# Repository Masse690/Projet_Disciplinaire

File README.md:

# Projet Smart Campus

Projet de terminal connecté intelligent développé dans le cadre du **Projet Disciplinaire M2** à l'Université Côte d'Azur.

Ce dépôt rassemble les documents de conception d'un nœud IoT alimenté par récupération d'énergie solaire. Le démonstrateur associera un module LoRaWAN RAK3172, un gestionnaire d'énergie bq25570, un stockage d'énergie et un ou plusieurs capteurs pour surveiller un environnement du campus.

> **Statut actuel :** sujet, architecture de base et datasheets disponibles. Le firmware, la conception KiCad, le PCB, l'antenne, le boîtier 3D et les résultats de démonstration restent à ajouter.

---

## Vue d'ensemble

L'objectif du projet est de concevoir un objet connecté autonome, depuis le choix des composants jusqu'à sa validation sur le réseau LoRaWAN.

Le projet couvre les étapes suivantes :

- conception du hardware avec KiCad ;
- intégration de capteurs ;
- développement du firmware embarqué ;
- conception et optimisation de l'antenne ;
- création d'un boîtier imprimé en 3D ;
- alimentation par panneau solaire ;
- stockage de l'énergie dans un supercondensateur ou une batterie ;
- fabrication du PCB ;
- assemblage des composants ;
- déploiement d'une démonstration sur une durée de une à deux semaines ;
- validation des communications et de la consommation énergétique.

### Architecture cible

```text
Panneau solaire
      |
      v
   bq25570
   +------+
   |      +--> stockage d'énergie
   |      |    (supercondensateur ou batterie)
   |      |
   |      +--> alimentation 3,3 V
   +------+
      |
      v
+-------------------+
| RAK3172 / STM32WL|<--> antenne LoRa 868 MHz
+-------------------+
      |
      +--> capteur(s) I2C/UART
```

---

## Équipe

| Nom | Rôle |
|---|---|
| Noé Massé | Firmware, électronique, capteurs, réseau |
| Alec Passolunghi | Conception PCB, boîtier 3D |
| Matis Chevreaux | Antenne |

**Encadrement :** 
- Fabien Ferrero — Université Côte d'Azur / CNRS / LEAT
- Dorian Diana — Université Côte d'Azur / LEAT
---

## Cas d'application

Le sujet propose l'utilisation d'au moins un capteur spécifique au projet. Les ressources initiales du dépôt comprennent une datasheet pour le capteur de gaz MQ-2.

Usages possibles :

- détection de fumée dans une salle ;
- surveillance de la qualité de l'air ;
- détection de fuite de gaz ;
- alerte de sécurité dans un bâtiment ;

L'application retenue, .... à definir

---

## Architecture matérielle

### Contrôleur et radio

Le **RAK3172** est un module LoRaWAN compact basé sur le microcontrôleur STM32WLE5CC.

Caractéristiques principales :

- cœur ARM Cortex-M4 jusqu'à 48 MHz ;
- radio LoRa / LoRaWAN ;
- support LoRaWAN 1.0.3 ;
- modes OTAA et ABP ;
- communication P2P ;
- interfaces UART, I2C et GPIO ;
- tension d'alimentation comprise entre 2,0 V et 3,6 V ;
- connexion à une antenne 868 MHz par réseau RF dédié.

Exemples de consommations indiquées dans la datasheet :

| Mode | Valeur indicative |
|---|---:|
| Sleep | 1,69 µA |
| Réception | 5,22 mA |
| Émission | environ 87 mA à 20 dBm |

La valeur finale devra être mesurée sur le prototype assemblé.

### Gestion d'énergie

Le **bq25570** est un chargeur ultra-faible consommation pour applications alimentées par récupération d'énergie.

Fonctions principales :

- démarrage à froid à partir d'environ 600 mV ;
- fonctionnement normal à partir d'environ 100 mV ;
- suivi du point de puissance maximale programmable ;
- protection de la tension de batterie ;
- sortie buck régulée ;
- surcharge, sous-charge et gestion du stockage.

L'étage bq25570 doit permettre d'alimenter la charge électronique pendant les périodes de faible ensoleillement grâce à un stockage tampon.

### Stockage d'énergie

Deux solutions peuvent être utilisées :

- supercondensateur ;
- batterie rechargeable.

La datasheet du bq25570 indique qu'une capacité équivalente d'au moins 100 µF est nécessaire. Le stockage, sa tension maximale, sa capacité utile et ses limites de charge devront être choisis selon le profil d'utilisation.

### Capteur MQ-2

Le MQ-2 est un capteur semi-conducteur sensible aux gaz combustibles et à la fumée.

Gaz détectables :

- GPL ;
- propane ;
- butane ;
- méthane ;
- hydrogène ;
- alcool ;
- fumée ;
- monoxyde de carbone.

Considérations d'intégration :

- alimentation/heater : environ 5 V ;
- consommation du heater : inférieure à 800 mW ;
- résistance de détection typique : 3 à 30 kΩ ;
- préchauffage recommandé : au moins 24 heures ;
- calibration nécessaire avec des concentrations de gaz connues ;
- densité de gaz à confirmer dans l'utilisation finale.

Le MQ-2 est principalement adapté à une détection relative. Les valeurs brutes doivent être calibrées plutôt que directement interprétées comme une concentration précise.

---

## Développement logiciel

La plateforme peut être programmée depuis l'environnement Arduino ou depuis les outils ST, selon le firmware retenu.

Fonctions prévues :

- initialisation du RAK3172 ;
- activation LoRaWAN ;
- acquisition périodique des capteurs ;
- conversion et calibration des mesures ;
- gestion des valeurs limites ;
- transmission via OTAA ou ABP ;
- gestion des accusés de réception ;
- configuration des périodes de sommeil ;
- adaptation du taux de transmission ;
- surveillance de la tension de stockage ;
- journalisation des événements.

Des exemples de scripts, d'envoi de données et de visualisation pourront être ajoutés dans ce dépôt lorsque l'application sera implémentée.

---

## Communications LoRaWAN

Le nœud pourra joindre un réseau LoRaWAN en utilisant OTAA ou ABP.

Les informations suivantes devront être définies pour chaque déploiement :

- région LoRaWAN ;
- identifiants OTAA ou clés ABP ;
- classe de terminal ;
- fréquence d'émission ;
- facteur d'étalement ;
- bande passante ;
- cycle de mesure ;
- payload ;
- serveur réseau ;
- application Node-RED ou serveur de visualisation.

Les clés réseau ne doivent jamais être publiées dans ce dépôt. Elles devront être stockées dans un fichier ignoré par Git ou injectées localement lors de la compilation.

---

## Antenne et conception du boîtier

### Antenne

La carte devra intégrer une solution adaptée à la fréquence choisie, généralement 868 MHz en Europe.

Travaux à réaliser :

- étude de l'impédance ;
- choix du type d'antenne ;
- optimisation dans son environnement réel ;
- mesure du diagramme ou de l'adaptation si un équipement est disponible ;
- distance entre l'antenne, le plan de masse, le panneau solaire et les composants sensibles.

### Boîtier

Le boîtier imprimé en 3D devra :

- protéger l'électronique ;
- permettre le passage ou l'intégration de l'antenne ;
- protéger le capteur tout en laissant l'air circuler ;
- faciliter l'orientation du panneau solaire ;
- permettre l'accès aux connecteurs de programmation ;
- intégrer des éventuelles fixations pour le Smart Campus.

---

## Conception PCB

La carte finale sera conçue avec KiCad et réalisée pour l'assemblage du démonstrateur.

Livrables attendus :

- schéma électrique ;
- annotation des composants ;
- liste BOM ;
- routage du PCB ;
- fichiers Gerber ;
- fichier de perçage ;
- fichiers Pick-and-Place ;
- plan de masse ;
- respect de l'intégrité RF ;
- plan d'essai et de programmation ;
- documentation d'assemblage.

Ces fichiers seront ajoutés au dépôt une fois la première révision validée.

---

## Structure du dépôt

```text
.
├── Data_sheet/                 # Datasheets des composants
│   ├── 605-00008-MQ-2-Datasheet-370464.pdf
│   ├── bq25570.pdf
│   └── RAK3172.pdf
├── Projet SMART CAMPUS_27.pdf  # Sujet du projet
└── README.md
```

Structure cible :

```text
.
├── hardware/
│   ├── schematics/
│   ├── kicad/
│   ├── gerber/
│   ├── bom/
│   └── 3d/
├── datasheets/
├── firmware/
├── application/
├── tests/
├── photos/
└── README.md
```

---

## Tests et validation

Les validations prévues comprennent :

- vérification du schéma et du routage ;
- test de démarrage du bq25570 ;
- mesure des tensions de stockage ;
- test du buck 3,3 V ;
- test de préchauffage du MQ-2 ;
- calibration du capteur ;
- vérification du courant sommeil ;
- mesure du courant de réception ;
- mesure du courant d'émission ;
- test OTAA ou ABP ;
- validation de la portée ;
- démonstration extérieure ;
- analyse de l'autonomie sur plusieurs jours ;
- mesures de consommation avec les temporisations réelles.

Les résultats seront accompagnés de captures, tableaux ou graphiques dès qu'ils seront disponibles.

---

## Installation

### Prérequis prévus

- Arduino IDE avec le cœur RAKwireless, ou environnement STM32 compatible ;
- KiCad pour consulter ou modifier les fichiers hardware ;
- outil de terminal série ;
- compte réseau LoRaWAN ;
- chaîne d'alimentation solaire adaptée ;
- chargeur ou alimentation pour les essais.

### Firmware

Le firmware n'est pas encore ajouté au dépôt. Une fois disponible, cette section devra fournir :

```text
git clone https://github.com/Masse690/Projet_Disciplinaire.git
cd Projet_Disciplinaire
```

Puis les instructions exactes d'installation des dépendances, de compilation et de téléversement.

---

## Critères d'évaluation

| Critère | Pondération |
|---|---:|
| Technique : complexité du système | 30 % |
| Applicabilité : maturité et utilité du démonstrateur | 25 % |
| Présentation : qualité, clarté et réponses aux questions | 25 % |
| Consommation : optimisation énergétique | 20 % |

---

## Planning

| Période | Travaux |
|---|---|
| Phase actuelle | Analyse du sujet, composants et architecture |
| À venir | Sélection finale du cas d'application et du capteur |
| À venir | Modélisation et conception de l'antenne |
| À venir | Développement du firmware |
| À venir | Conception PCB sous KiCad |
| Décembre 2026 | Finalisation de la carte électronique |
| Janvier 2027 | Fabrication de la carte |
| À venir | Assemblage avec pochoir et four à fusion |
| À venir | Tests électriques, LoRaWAN et autonomie |
| À venir | Déploiement sur une à deux semaines |

---

## Ressources

- [Sujet du projet](Projet%20SMART%20CAMPUS_27.pdf)
- [Datasheet RAK3172](Data_sheet/RAK3172.pdf)
- [Datasheet bq25570](Data_sheet/bq25570.pdf)
- [Datasheet MQ-2](Data_sheet/605-00008-MQ-2-Datasheet-370464.pdf)
- [Documentation RAK3172](https://docs.rakwireless.com/product-categories/wisduo/rak3172-module/overview/)
- [Documentation Texas Instruments bq25570](https://www.ti.com/product/BQ25570)
- [Exemple de plateforme EDU RAK 2026](https://github.com/DorianDIANA/EDU_RAK_2026)

---

## Démonstration

Des images, vidéos, résultats de portée, graphiques de consommation et données du réseau seront ajoutés après les premiers essais.

## Licence

Licence à définir avant la diffusion publique du projet.

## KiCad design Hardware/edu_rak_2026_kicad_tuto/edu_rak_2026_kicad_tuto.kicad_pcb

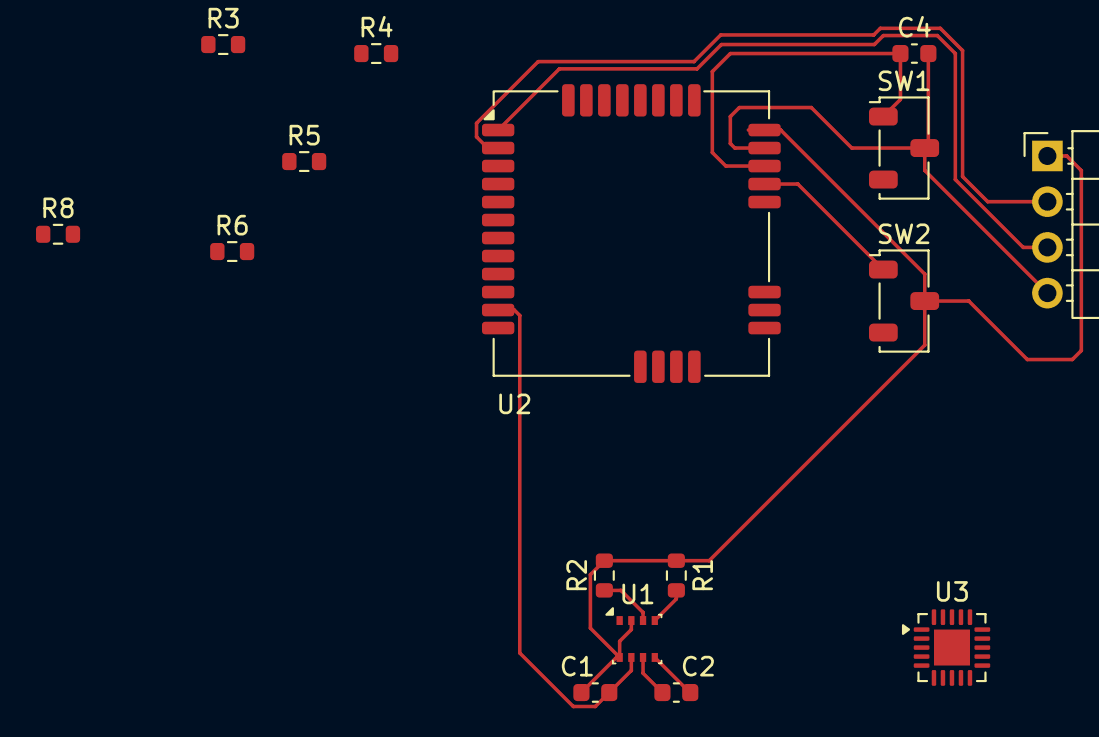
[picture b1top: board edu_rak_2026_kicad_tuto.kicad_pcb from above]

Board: 4 copper layers, 16 parts (0 on the bottom side), 12 nets.

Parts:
C1, C2, C4: 100nf; C_0603_1608Metric
J1: Conn_01x04_Pin; PinHeader_1x04_P2.54mm_Horizontal
R1, R2: 4k7; R_0603_1608Metric
R3: 0R; R_0603_1608Metric
R4: 100K; R_0603_1608Metric
R5, R6, R8: R; R_0603_1608Metric
SW1, SW2: SW_SPST; Nidec_Copal_CAS-120A
U1: BME280; Bosch_LGA-8_2.5x2.5mm_P0.65mm_ClockwisePinNumbering
U2: RAK3172-xx-8-SM-xI; RAK3172
U3: BQ25570; QFN-20-1EP_3.5x3.5mm_P0.5mm_EP2x2mm

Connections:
/MCU/BOOT: R4.1, SW2.1 (A), U2.21 (BOOT0)
/MCU/RF: R3.1, U2.12 (RF)
/MCU/RST: C4.1, SW1.1 (A), U2.22 (~RST)
/MCU/UART_RX: J1.3, U2.1 (UART2_RX/PA3)
/MCU/UART_TX: J1.2, U2.2 (UART2_TX/PA2)
GND: C1.2, C2.2, C4.2, J1.4, R4.2, R5.2, R6.2, SW1.2 (B), U1.1 (GND), U1.5 (SDO), U1.7 (GND), U2.11 (GND), U2.17 (GND), U2.18 (GND), U2.23 (GND), U2.28 (GND)
unnamed: R5.1, R8.1
unnamed: R3.2, R6.1, R8.2
unnamed: U3.1 (VSS), U3.9 (VSS), U3.15 (VSS), U3.17 (VSS), U3.21 (VSS)
SCL: R1.1, U1.4 (SCK), U2.9 (PA12/SCL)
SDA: R2.1, U1.3 (SDI), U2.10 (PA11/SDA)
VCC: C1.1, C2.1, J1.1, R1.2, R2.2, SW2.2 (B), U1.2 (CSB), U1.6 (VDDIO), U1.8 (VDD), U2.24 (VDD)
